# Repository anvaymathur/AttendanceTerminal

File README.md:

# Attendance Terminal

The attendance terminal is a compact, standalone barcode terminal for tracking school club attendance. 
Students scan their existing school ID card, and the terminal sends the scan over Wi-Fi to a backend server that records attendance.

I built this project to participate in [Hack Club's Half-Life YSWS](https://halflife.hackclub.com)

## Description
________________________________

The attendance terminal is there to solve a big issue at my school. Most clubs and teams at our school track attendance, either for how long you have been there 
or just to make sure you attend. However, there is no centralized way to do attendance. Some do it on paper, some have their own system, but it is overall very uncoordinated.
This project aims to fix that by having an unified hardware scanner module for every club. Then, on a seperate web-app (not currently included) a student would link their information to their student card number, which exists in the form of a barcode on their student card. Then the student can choose to scan their student card, or the qr code
generated on the web-app to sign in. For each club, there would be an admin portal where the club admin would input the external information the club wants. For example, if
there is a tutoring club, they would want to know whether you are a tutor or a student. So before signing in, the student would go into the club's portal on the web-app and fill
in any additional information the clubs want. The attendance information for each club is only shown to the club admin, so the student will have multiple attendance records for 
various clubs. 

## Features
________________________________
* 3D Printed Case
* RGB Status LED
* Buzzer for audio confirmation 
* OLED display for text
* Custom PCB
* Battery Powered
* Optional USB-C Wired connection while charging battery

## PCB
________________________________
Custom PCB Made in KiCad. Some footprints and schematics were from [marbastlib](https://github.com/ebastler/marbastlib). 

## CAD
________________________________
Custom 3D-Printable CAD for the case, which houses the project. It is in 3 parts, the base, which houses the battery, the power switch and has the holes for the usb-c cable connection. The lid which is what the PCB screws onto, has legs that extend out to allow the top of the pcb to have room for the components. It also has cutouts for the Display, Scanner module, LED and Buzzer. Lastly there is a stand that allows the whole box to sit at an angle to make it easier to scan.

## Firmware
________________________________
There is custom firmware written currently for scanning the barcode or qrcode and displaying the code on the screen, with an audible beep and status light confirmation status.
The current firmware is not in its final stage and does not include the wifi capabilites as I will need to build the backend and the web app it connects to first. The firmware can be found in the firmware folder, main.py

# Bill of Materials (BOM)
________________________________
Here is everything that you will need to make the attendance terminal: [Click here](https://docs.google.com/spreadsheets/d/1CIG54QZLjPgN8hb-R9MU0n-KgLEakrtmUqO80z-3FYI/edit?usp=sharing)

| Item                                              | Description     | Preowned | Of sets | Pcs set | Price set usd | Item total price tax shipping usd                                                                               | Supplier   | Url                                                                                                                                                                                                                                                                                                                                            |
| :------------------------------------------------ | :-------------- | :------- | :------ | :------ | :------------ | :-------------------------------------------------------------------------------------------------------------- | :--------- | :--------------------------------------------------------------------------------------------------------------------------------------------------------------------------------------------------------------------------------------------------------------------------------------------------------------------------------------------- |
| Megaboard PCB Printing with JLCPCB                | PCB             | FALSE    | 1       | 5       | $4.00         | $10.45                                                                                                          | JLCPCB     | https://github.com/anvaymathur/AttendanceTerminal/blob/main/Assets/PCBPrice.png                                                                                                                                                                                                                                                                |
| GM861S UART/USB QR Code Barcode Scanner Module    | Scanner         | FALSE    | 1       | 1       | $12.06        | $19.36                                                                                                          | Aliexpress | https://www.aliexpress.com/item/1005004625447564.html?spm=a2g0o.cart.0.0.406938daaYfxhp&mp=1&pdp_npi=6%40dis%21USD%21USD+12.70%21USD+12.06%21%21USD+12.06%21%21%21%402101d9ef17917595512443088e0fa2%2112000049687924342%21ct%21CA%218080657096%21%211%210%21                                                                                   |
| 2N7000 MOSFET Transistors                         | Transistor      | TRUE     | 1       | 50      | $3.25         | $3.25                                                                                                           | Aliexpress | https://www.aliexpress.com/item/1005010455877756.html?spm=a2g0o.cart.0.0.406938daaYfxhp&mp=1&pdp_npi=6%40dis%21USD%21USD+3.25%21USD+1.19%21%21USD+1.19%21%21%21%402101e5ab17917587327662497e0cf4%2112000052472892653%21ct%21CA%218080657096%21%211%210%21                                                                                      |
| Male Female Pin Header Single Row 2.54mm          | Header Pins     | TRUE     | 1       | 20      | $10.51        | $10.51                                                                                                          | Aliexpress | https://www.aliexpress.com/item/1005003642939564.html?spm=a2g0o.cart.0.0.406938daaYfxhp&mp=1&pdp_npi=6%40dis%21USD%21USD+10.51%21USD+10.51%21%21USD+10.51%21%21%21%402101e5ab17917588011244964e0cf4%2112000026620972925%21ct%21CA%218080657096%21%211%210%21&pdp_ext_f=%7B%22cart2PdpParams%22%3A%7B%22pdpBusinessMode%22%3A%22retail%22%7D%7D |
| Mini Vertical Micro Slide Switch                  | Power Switch    | TRUE     | 1       | 100     | $4.22         | $4.22                                                                                                           | Aliexpress | https://www.aliexpress.com/item/1005012254659077.html?spm=a2g0o.cart.0.0.406938daaYfxhp&mp=1&pdp_npi=6%40dis%21USD%21USD+8.45%21USD+4.22%21%21USD+4.22%21%21%21%4021033b3317917594057515630e0d76%2112000057879053223%21ct%21CA%218080657096%21%211%210%21                                                                                      |
| PH2.0 JST Male Female Plug Socket                 | Connectors      | TRUE     | 1       | 180     | $5.74         | $5.74                                                                                                           | Aliexpress | https://www.aliexpress.com/item/1005010504133815.html?spm=a2g0o.cart.0.0.406938daaYfxhp&mp=1&pdp_npi=6%40dis%21USD%21USD+11.96%21USD+5.74%21%21USD+5.74%21%21%21%402101d9ef17917595642223576e0fa2%2112000052613306875%21ct%21CA%218080657096%21%211%210%21                                                                                     |
| Aluminum Electrolytic Capacitor                   | Capcitor        | TRUE     | 1       | 40      | $3.01         | $3.01                                                                                                           | Aliexpress | https://www.aliexpress.com/item/1005011811368397.html?spm=a2g0o.cart.0.0.406938daaYfxhp&mp=1&pdp_npi=6%40dis%21USD%21USD+3.01%21USD+1.19%21%21USD+1.19%21%21%21%402101d9ef17917595512443088e0fa2%2112000056639843395%21ct%21CA%218080657096%21%211%210%21                                                                                      |
| Resistor Assortment Kit                           | Resistors       | TRUE     | 1       | 300     | $4.03         | $4.03                                                                                                           | Aliexpress | https://www.aliexpress.com/item/1005010779049132.html?spm=a2g0o.cart.0.0.406938daaYfxhp&mp=1&pdp_npi=6%40dis%21USD%21USD+8.23%21USD+1.19%21%21USD+1.19%21%21%21%402101d9ef17917595512443088e0fa2%2112000053480061365%21ct%21CA%218080657096%21%211%210%21                                                                                      |
| Diffused Cathode RGB LED                          | RGB LED         | TRUE     | 1       | 50      | $4.49         | $4.49                                                                                                           | Aliexpress | https://www.aliexpress.com/item/1005011597522333.html?spm=a2g0o.cart.0.0.406938daaYfxhp&mp=1&pdp_npi=6%40dis%21USD%21USD+8.98%21USD+4.49%21%21USD+4.49%21%21%21%402101d9ef17917598161385593e0fa2%2112000056017941722%21ct%21CA%218080657096%21%211%210%21                                                                                      |
| 3V Active Buzzer Magnetic                         | Buzzer          | TRUE     | 1       | 10      | $3.29         | $3.29                                                                                                           | Aliexpress | https://www.aliexpress.com/item/1005012105971644.html?spm=a2g0o.cart.0.0.406938daaYfxhp&mp=1&pdp_npi=6%40dis%21USD%21USD+6.58%21USD+3.29%21%21USD+3.29%21%21%21%402101d9ef17917598354986444e0fa2%2112000057527255015%21ct%21CA%218080657096%21%211%210%21                                                                                      |
|  IIC OLED Display Module                          | OLED Screen     | TRUE     | 1       | 1       | $3.34         | $3.34                                                                                                           | Aliexpress | https://www.aliexpress.com/item/1005008934254841.html?spm=a2g0o.cart.0.0.406938daaYfxhp&mp=1&pdp_npi=6%40dis%21USD%21USD+3.34%21USD+1.19%21%21USD+1.19%21%21%21%402101d9ef17917595512443088e0fa2%2112000047263287878%21ct%21CA%218080657096%21%211%210%21                                                                                      |
| seeed XIAO ESP32-S3 Mini Development Board Module | Microcontroller | TRUE     | 1       | 1       | $16.90        | $16.90                                                                                                          | Aliexpress | https://www.aliexpress.com/item/1005008813495235.html?spm=a2g0o.cart.0.0.406938daaYfxhp&mp=1&pdp_npi=6%40dis%21USD%21USD+36.74%21USD+16.90%21%21USD+16.90%21%21%21%402101d9ef17917600600567357e0fa2%2112000046840040809%21ct%21CA%218080657096%21%211%210%21                                                                                   |
|  3.7V 110mAh 301230 JST PH 2.0mm LiPo Battery     | Battery         | TRUE     | 1       | 2       | $10.94        | $10.94                                                                                                          | Aliexpress | https://www.aliexpress.com/item/1005010595321382.html?spm=a2g0o.cart.0.0.1f2038daooOQB6&mp=1&pdp_npi=6%40dis%21USD%21USD+11.89%21USD+10.94%21%21USD+10.94%21%21%21%402101d9ef17917603080878977e0fa2%2112000052929761860%21ct%21CA%218080657096%21%211%210%21                                                                                   |
| Grand Total:                                      |                 |          |         |         | $85.78        |  |            |                                                                                                                                                                                                                                                                                                                                                |
|                                                   |                 |          |         |         |               |                                                                                                                 |            |                                                                                                                                                                                                                                                                                                                                                |

# Thank you

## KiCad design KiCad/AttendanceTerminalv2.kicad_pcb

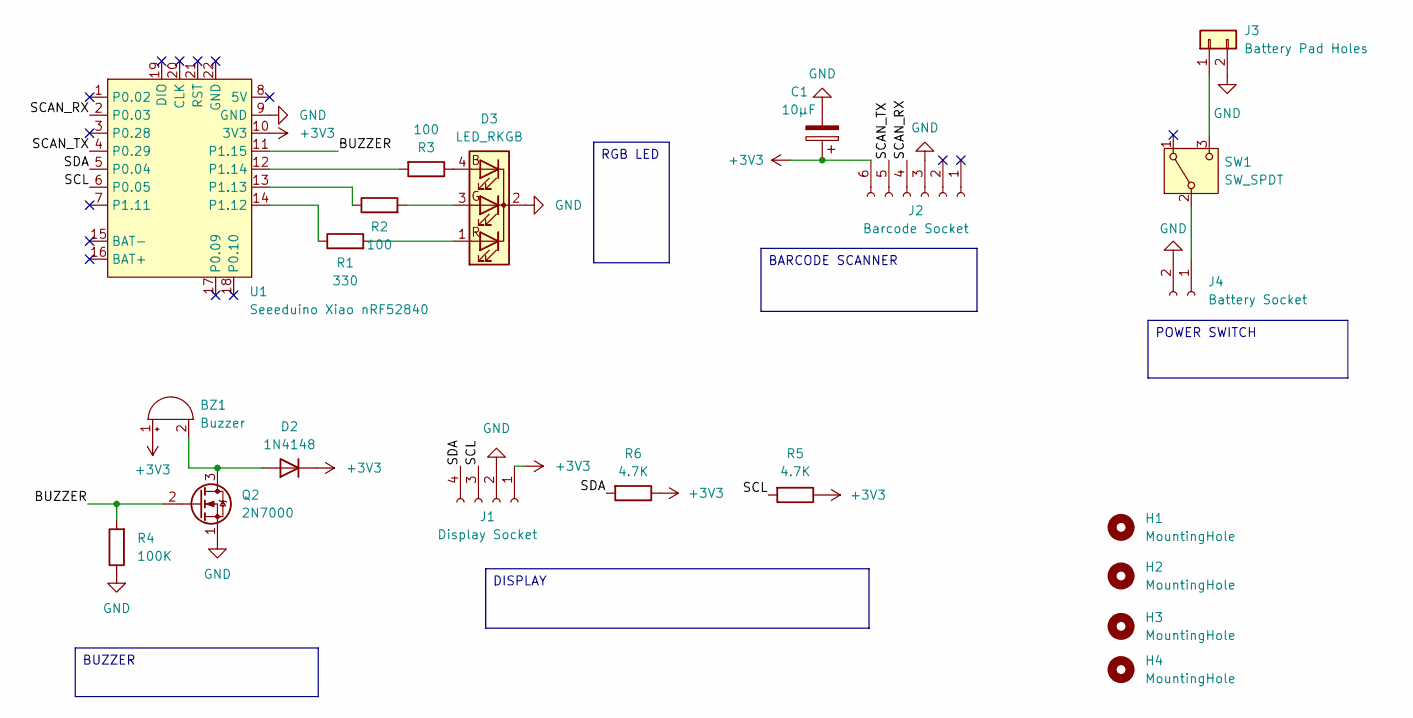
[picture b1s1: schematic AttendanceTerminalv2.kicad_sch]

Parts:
BZ1: Buzzer; Buzzer_12x9.5RM7.6
C1: 10µF; CP_Radial_D5.0mm_P2.00mm
D2: 1N4148; D_DO-35_SOD27_P7.62mm_Horizontal
D3: LED_RKGB; LED_D5.0mm-4_RGB_Wide_Pins
H1, H2, H3, H4: MountingHole; MountingHole_3.2mm_M3
J1: Display Socket; PinSocket_1x04_P2.54mm_Vertical
J2: Barcode Socket; PinHeader_1x06_P2.54mm_Vertical
J3: Battery Pad Holes; PinHeader_1x02_P2.54mm_Vertical
J4: Battery Socket; JST_PH_B2B-PH-K_1x02_P2.00mm_Vertical
Q2: 2N7000; TO-92_Inline
R1: 330; R_Axial_DIN0207_L6.3mm_D2.5mm_P10.16mm_Horizontal
R2, R3: 100; R_Axial_DIN0207_L6.3mm_D2.5mm_P10.16mm_Horizontal
R4: 100K; R_Axial_DIN0207_L6.3mm_D2.5mm_P10.16mm_Horizontal
R5, R6: 4.7K; R_Axial_DIN0207_L6.3mm_D2.5mm_P10.16mm_Horizontal
SW1: SW_SPDT; PinHeader_1x03_P2.54mm_Vertical
U1: Seeeduino Xiao nRF52840; Xiao_nRF52840_ACH

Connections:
+3V3: BZ1.1 (+), C1.1, D2.1 (K), J1.1, J2.6, R5.1, R6.1, U1.10 (3V3)
/BUZZER: Q2.2 (G), R4.2, U1.11 (P1.15)
/SCAN_RX: J2.4, U1.2 (P0.03)
/SCAN_TX: J2.5, U1.4 (P0.29)
/SCL: J1.3, R5.2, U1.6 (P0.05)
/SDA: J1.4, R6.2, U1.5 (P0.04)
GND: C1.2, D3.2 (K), J1.2, J2.3, J3.2, J4.2, Q2.1 (S), R4.1, U1.9 (GND)
unnamed: BZ1.2 (-), D2.2 (A), Q2.3 (D)
unnamed: D3.4 (BA), R3.1
unnamed: D3.3 (GA), R2.2
unnamed: D3.1 (RA), R1.2
unnamed: J3.1, SW1.3 (C)
unnamed: J4.1, SW1.2 (B)
unnamed: R1.1, U1.14 (P1.12)
unnamed: R2.1, U1.13 (P1.13)
unnamed: R3.2, U1.12 (P1.14)

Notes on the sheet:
DISPLAY
RGB LED
POWER SWITCH
BUZZER
BARCODE SCANNER

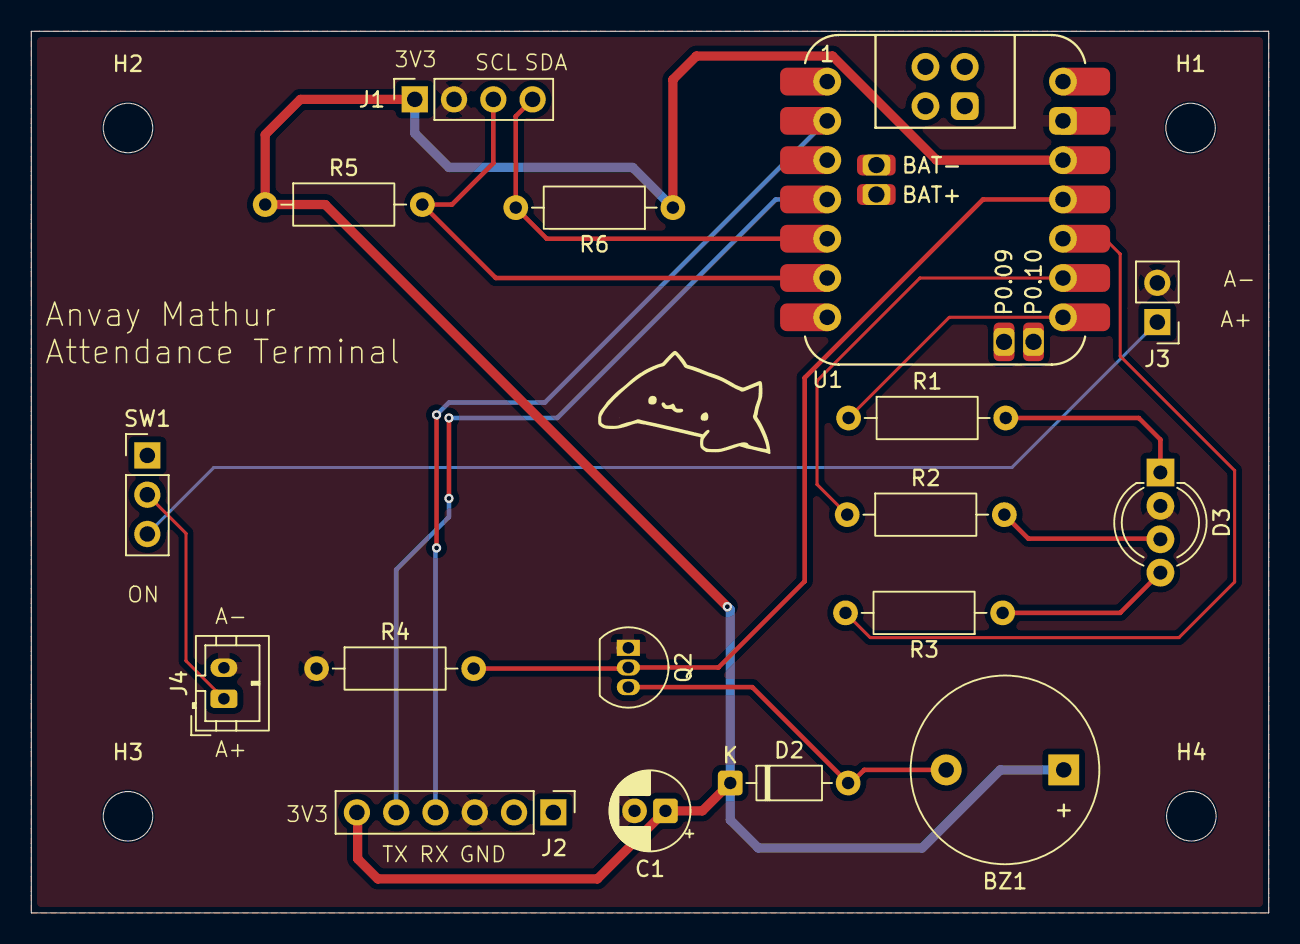
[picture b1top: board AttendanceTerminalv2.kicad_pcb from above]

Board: 2 copper layers, 80.0 x 57.0 mm, 21 parts (0 on the bottom side), 16 nets.
